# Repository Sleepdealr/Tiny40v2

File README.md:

# Tiny40v2

Please read the license.
Licensed under the Attribution-NonCommercial-ShareAlike 4.0 International

40% PCB with the equinox layout

Using the RP2040

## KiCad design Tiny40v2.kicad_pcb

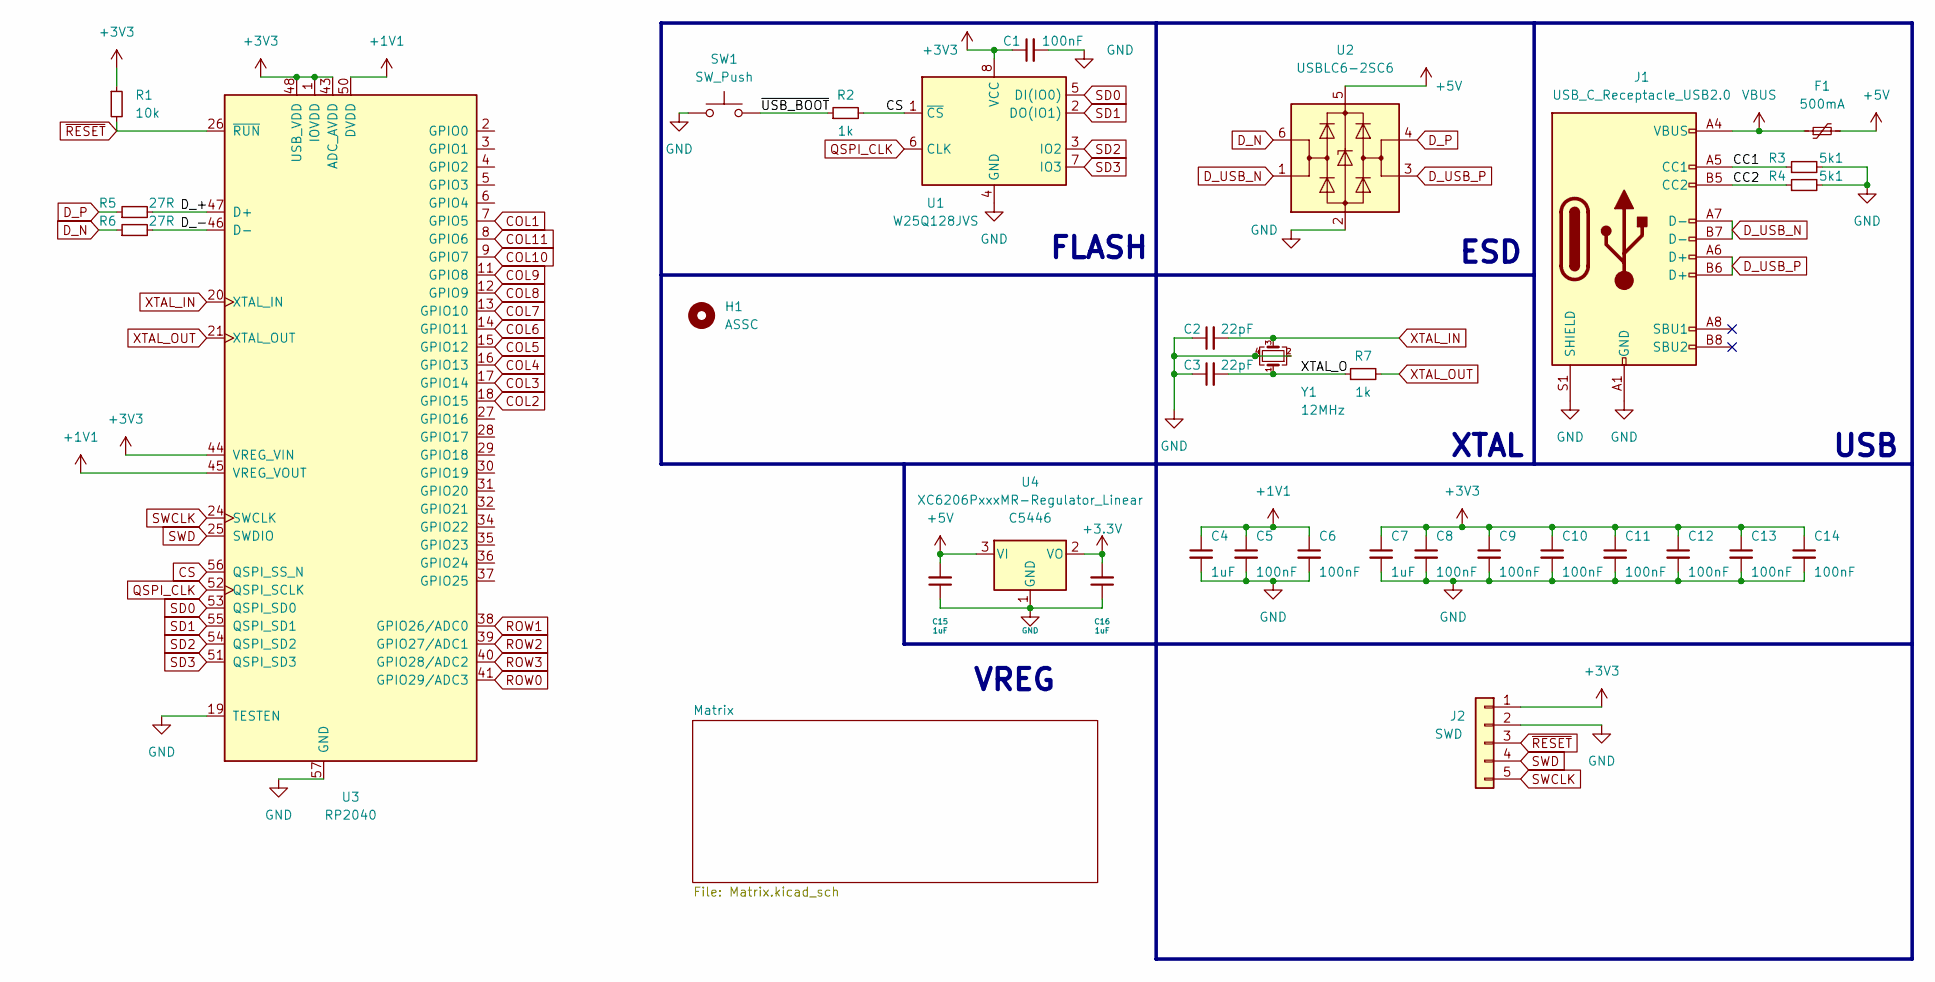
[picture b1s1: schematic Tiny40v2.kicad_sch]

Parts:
C1, C5, C6, C8, C9, C10, C11, C12, C13, C14: 100nF; C_0402_1005Metric; LCSC C1525
C2, C3: 22pF; C_0402_1005Metric; LCSC C1555
C4, C7, C15, C16: 1uF; C_0402_1005Metric; LCSC C52923
F1: 500mA; Fuse_1206_3216Metric; LCSC C70076
H1: ASSC; assc_fixed
J1: USB_C_Receptacle_USB2.0; USB_C_Receptacle_HRO_TYPE-C-31-M-12; LCSC C165948
J2: SWD; PinSocket_1x05_P2.54mm_Vertical
R1: 10k; R_0402_1005Metric; LCSC C25744
R2, R7: 1k; R_0402_1005Metric; LCSC C11702
R3, R4: 5k1; R_0402_1005Metric; LCSC C25905
R5, R6: 27R; R_0603_1608Metric; LCSC C25190
SW1: SW_Push; PinSocket_1x02_P2.54mm_Vertical
U1: W25Q128JVS; SOIC-8_5.23x5.23mm_P1.27mm; LCSC C131025
U2: USBLC6-2SC6; SOT-23-6; LCSC C2827654
U3: RP2040; RP2040-QFN-56; LCSC C2040
U4: XC6206PxxxMR-Regulator_Linear; SOT-23; LCSC C5446
Y1: 12MHz; Crystal_SMD_3225-4Pin_3.2x2.5mm; LCSC C97242

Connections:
+1V1: C4.1, C5.1, C6.1, U3.23 (DVDD), U3.45 (VREG_VOUT), U3.50 (DVDD)
+5V: C15.2, F1.2, U2.5 (VBUS), U4.3 (VI)
/CC1: J1.A5 (CC1), R3.1
/CC2: J1.B5 (CC2), R4.1
/D_+: R5.2, U3.47 (D+)
/D_-: R6.2, U3.46 (D-)
/XTAL_O: C3.2, R7.1, Y1.1
/~USB_BOOT: R2.1, SW1.2
COL1: U3.7 (GPIO5); also elsewhere on the board
COL2: U3.18 (GPIO15); also elsewhere on the board
COL3: U3.17 (GPIO14); also elsewhere on the board
COL4: U3.16 (GPIO13); also elsewhere on the board
COL5: U3.15 (GPIO12); also elsewhere on the board
COL6: U3.14 (GPIO11); also elsewhere on the board
COL7: U3.13 (GPIO10); also elsewhere on the board
COL8: U3.12 (GPIO9); also elsewhere on the board
COL9: U3.11 (GPIO8); also elsewhere on the board
COL10: U3.9 (GPIO7); also elsewhere on the board
COL11: U3.8 (GPIO6); also elsewhere on the board
CS: R2.2, U1.1 (~CS), U3.56 (QSPI_SS_N)
D_N: R6.1, U2.6 (I/O1)
D_P: R5.1, U2.4 (I/O2)
D_USB_N: J1.A7 (D-), J1.B7 (D-), U2.1 (I/O1)
D_USB_P: J1.A6 (D+), J1.B6 (D+), U2.3 (I/O2)
GND: C1.2, C2.1, C3.1, C4.2, C5.2, C6.2, C7.2, C8.2, C9.2, C10.2, C11.2, C12.2, C13.2, C14.2, C15.1, C16.1, J1.A1 (GND), J1.A12 (GND), J1.B1 (GND), J1.B12 (GND), J1.S1 (SHIELD), J2.2, R3.2, R4.2, SW1.1, U1.4 (GND), U2.2 (GND), U3.19 (TESTEN), U3.57 (GND), U4.1 (GND), Y1.2, Y1.4
QSPI_CLK: U1.6 (CLK), U3.52 (QSPI_SCLK)
ROW0: U3.41 (GPIO29/ADC3); also elsewhere on the board
ROW1: U3.38 (GPIO26/ADC0); also elsewhere on the board
ROW2: U3.39 (GPIO27/ADC1); also elsewhere on the board
ROW3: U3.40 (GPIO28/ADC2); also elsewhere on the board
SD0: U1.5 (DI(IO0)), U3.53 (QSPI_SD0)
SD1: U1.2 (DO(IO1)), U3.55 (QSPI_SD1)
SD2: U1.3 (IO2), U3.54 (QSPI_SD2)
SD3: U1.7 (IO3), U3.51 (QSPI_SD3)
SWCLK: J2.5, U3.24 (SWCLK)
SWD: J2.4, U3.25 (SWDIO)
VBUS: F1.1, J1.A4 (VBUS), J1.A9 (VBUS), J1.B4 (VBUS), J1.B9 (VBUS)
XTAL_IN: C2.2, U3.20 (XTAL_IN), Y1.3
XTAL_OUT: R7.2, U3.21 (XTAL_OUT)
~RESET: J2.3, R1.2, U3.26 (~RUN)

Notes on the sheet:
USB
VREG
ESD
XTAL
FLASH

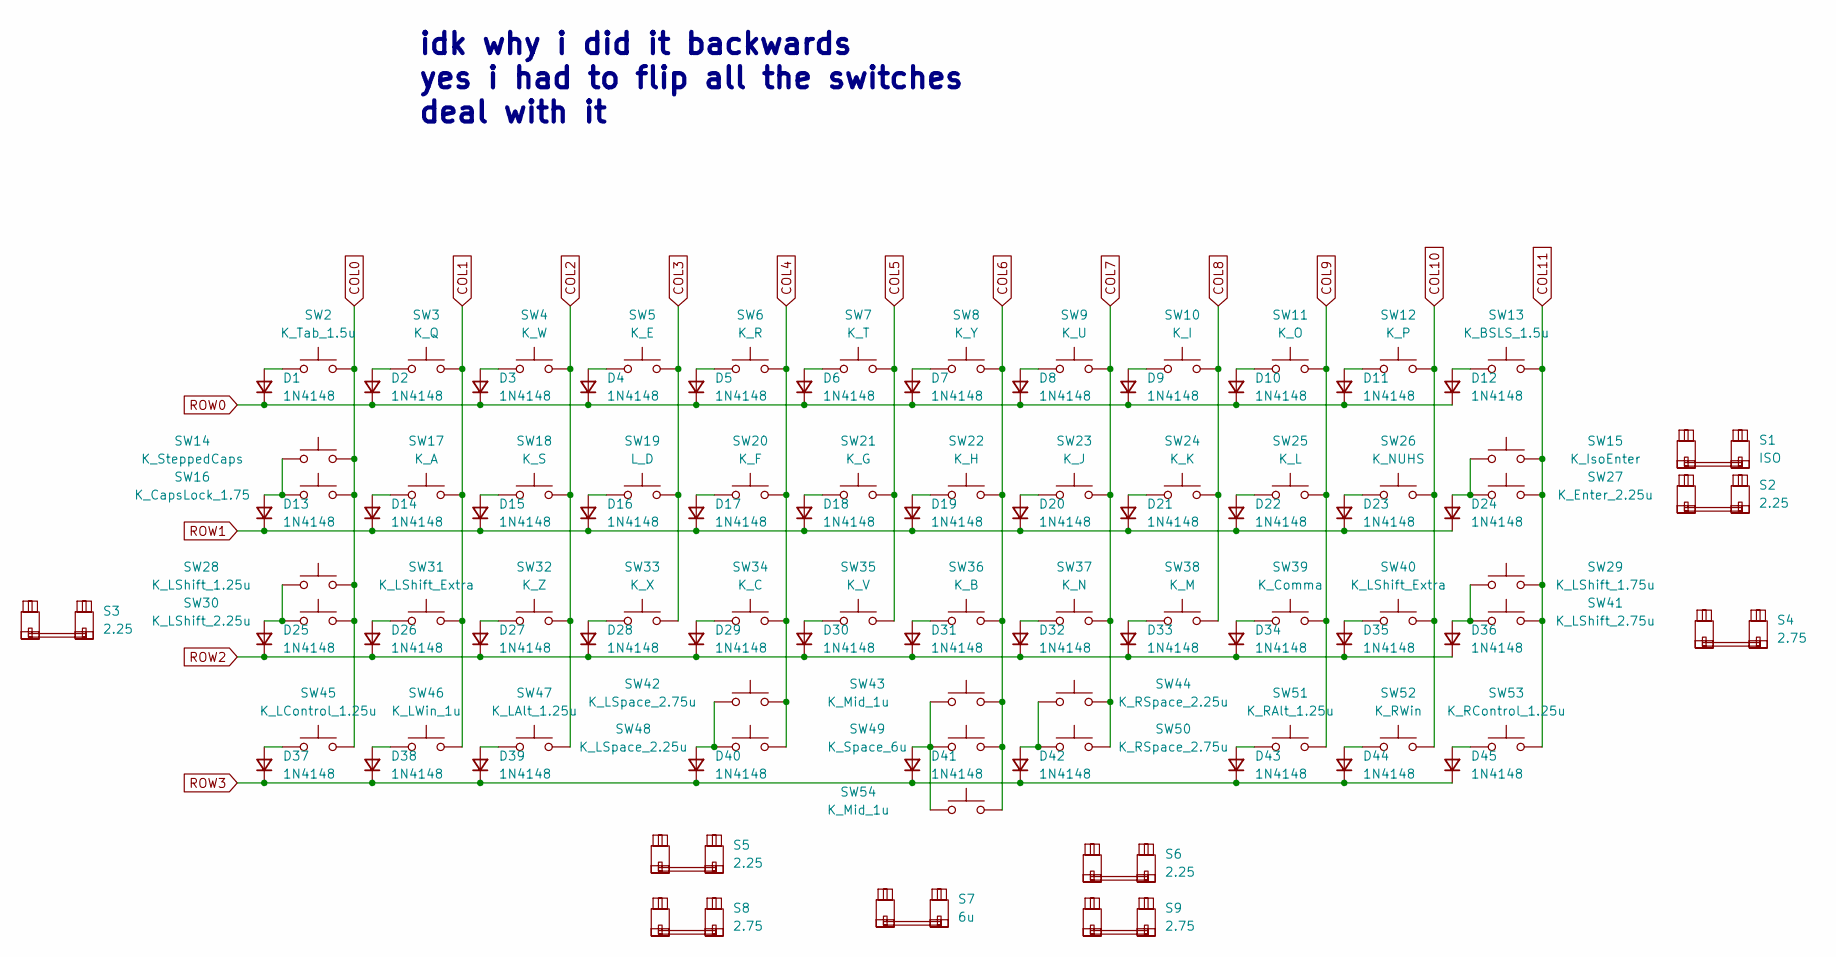
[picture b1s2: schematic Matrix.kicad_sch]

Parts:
D1, D2, D3, D4, D5, D6, D7, D8, D9, D10, D11, D12, D13, D14, D15, D16, D17, D18, D19, D20, D21, D22, D23, D24, D25, D26, D27, D28, D29, D30, D31, D32, D33, D34, D35, D36, D37, D38, D39, D40, D41, D42, D43, D44, D45: 1N4148; D_SOD-123
S1: ISO; STAB_MX_ISO_FLIPPED
S2, S3, S5, S6: 2.25; STAB_MX_2.25u
S4, S8, S9: 2.75; STAB_MX_2.75u
S7: 6u; STAB_MX_6u
SW2: K_Tab_1.5u; SW_MX_1.5u
SW3: K_Q; SW_MX_1u
SW4: K_W; SW_MX_1u
SW5: K_E; SW_MX_1u
SW6: K_R; SW_MX_1u
SW7: K_T; SW_MX_1u
SW8: K_Y; SW_MX_1u
SW9: K_U; SW_MX_1u
SW10: K_I; SW_MX_1u
SW11: K_O; SW_MX_1u
SW12: K_P; SW_MX_1u
SW13: K_BSLS_1.5u; SW_MX_1.5u
SW14: K_SteppedCaps; SW_MX_1.75u_stp
SW15: K_IsoEnter; SW_MX_1u
SW16: K_CapsLock_1.75; SW_MX_1.75u
SW17: K_A; SW_MX_1u
SW18: K_S; SW_MX_1u
SW19: L_D; SW_MX_1u
SW20: K_F; SW_MX_1u
SW21: K_G; SW_MX_1u
SW22: K_H; SW_MX_1u
SW23: K_J; SW_MX_1u
SW24: K_K; SW_MX_1u
SW25: K_L; SW_MX_1u
SW26: K_NUHS; SW_MX_1u
SW27: K_Enter_2.25u; SW_MX_1u
SW28: K_LShift_1.25u; SW_MX_1.25u
SW29: K_LShift_1.75u; SW_MX_1.75u
SW30: K_LShift_2.25u; SW_MX_1u
SW31, SW40: K_LShift_Extra; SW_MX_1u
SW32: K_Z; SW_MX_1u
SW33: K_X; SW_MX_1u
SW34: K_C; SW_MX_1u
SW35: K_V; SW_MX_1u
SW36: K_B; SW_MX_1u
SW37: K_N; SW_MX_1u
SW38: K_M; SW_MX_1u
SW39: K_Comma; SW_MX_1u
SW41: K_LShift_2.75u; SW_MX_1u
SW42: K_LSpace_2.75u; SW_MX_1u
SW43, SW54: K_Mid_1u; SW_MX_1u
SW44: K_RSpace_2.25u; SW_MX_1u
SW45: K_LControl_1.25u; SW_MX_1.25u
SW46: K_LWin_1u; SW_MX_1u
SW47: K_LAlt_1.25u; SW_MX_1.25u
SW48: K_LSpace_2.25u; SW_MX_1u
SW49: K_Space_6u; SW_MX_1u
SW50: K_RSpace_2.75u; SW_MX_1u
SW51: K_RAlt_1.25u; SW_MX_1.25u
SW52: K_RWin; SW_MX_1u
SW53: K_RControl_1.25u; SW_MX_1.25u

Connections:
COL0: SW2.1, SW14.1, SW16.1, SW28.1, SW30.1, SW45.1
COL1: SW3.1, SW17.1, SW31.1, SW46.1; also elsewhere on the board
COL2: SW4.1, SW18.1, SW32.1, SW47.1; also elsewhere on the board
COL3: SW5.1, SW19.1, SW33.1; also elsewhere on the board
COL4: SW6.1, SW20.1, SW34.1, SW42.1, SW48.1; also elsewhere on the board
COL5: SW7.1, SW21.1, SW35.1; also elsewhere on the board
COL6: SW8.1, SW22.1, SW36.1, SW43.1, SW49.1, SW54.1; also elsewhere on the board
COL7: SW9.1, SW23.1, SW37.1, SW44.1, SW50.1; also elsewhere on the board
COL8: SW10.1, SW24.1, SW38.1; also elsewhere on the board
COL9: SW11.1, SW25.1, SW39.1, SW51.1; also elsewhere on the board
COL10: SW12.1, SW26.1, SW40.1, SW52.1; also elsewhere on the board
COL11: SW13.1, SW15.1, SW27.1, SW29.1, SW41.1, SW53.1; also elsewhere on the board
unnamed: D1.2 (A), SW2.2
unnamed: D2.2 (A), SW3.2
unnamed: D3.2 (A), SW4.2
unnamed: D4.2 (A), SW5.2
unnamed: D5.2 (A), SW6.2
unnamed: D6.2 (A), SW7.2
unnamed: D7.2 (A), SW8.2
unnamed: D8.2 (A), SW9.2
unnamed: D9.2 (A), SW10.2
unnamed: D10.2 (A), SW11.2
unnamed: D11.2 (A), SW12.2
unnamed: D12.2 (A), SW13.2
unnamed: D13.2 (A), SW14.2, SW16.2
unnamed: D14.2 (A), SW17.2
unnamed: D15.2 (A), SW18.2
unnamed: D16.2 (A), SW19.2
unnamed: D17.2 (A), SW20.2
unnamed: D18.2 (A), SW21.2
unnamed: D19.2 (A), SW22.2
unnamed: D20.2 (A), SW23.2
unnamed: D21.2 (A), SW24.2
unnamed: D22.2 (A), SW25.2
unnamed: D23.2 (A), SW26.2
unnamed: D24.2 (A), SW15.2, SW27.2
unnamed: D25.2 (A), SW28.2, SW30.2
unnamed: D26.2 (A), SW31.2
unnamed: D27.2 (A), SW32.2
unnamed: D28.2 (A), SW33.2
unnamed: D29.2 (A), SW34.2
unnamed: D30.2 (A), SW35.2
unnamed: D31.2 (A), SW36.2
unnamed: D32.2 (A), SW37.2
unnamed: D33.2 (A), SW38.2
unnamed: D34.2 (A), SW39.2
unnamed: D35.2 (A), SW40.2
unnamed: D36.2 (A), SW29.2, SW41.2
unnamed: D37.2 (A), SW45.2
unnamed: D38.2 (A), SW46.2
unnamed: D39.2 (A), SW47.2
unnamed: D40.2 (A), SW42.2, SW48.2
unnamed: D41.2 (A), SW43.2, SW49.2, SW54.2
unnamed: D42.2 (A), SW44.2, SW50.2
unnamed: D43.2 (A), SW51.2
unnamed: D44.2 (A), SW52.2
unnamed: D45.2 (A), SW53.2
ROW0: D1.1 (K), D2.1 (K), D3.1 (K), D4.1 (K), D5.1 (K), D6.1 (K), D7.1 (K), D8.1 (K), D9.1 (K), D10.1 (K), D11.1 (K), D12.1 (K); also elsewhere on the board
ROW1: D13.1 (K), D14.1 (K), D15.1 (K), D16.1 (K), D17.1 (K), D18.1 (K), D19.1 (K), D20.1 (K), D21.1 (K), D22.1 (K), D23.1 (K), D24.1 (K); also elsewhere on the board
ROW2: D25.1 (K), D26.1 (K), D27.1 (K), D28.1 (K), D29.1 (K), D30.1 (K), D31.1 (K), D32.1 (K), D33.1 (K), D34.1 (K), D35.1 (K), D36.1 (K); also elsewhere on the board
ROW3: D37.1 (K), D38.1 (K), D39.1 (K), D40.1 (K), D41.1 (K), D42.1 (K), D43.1 (K), D44.1 (K), D45.1 (K); also elsewhere on the board

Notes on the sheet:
idk why i did it backwards yes i had to flip all the switches deal with it

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
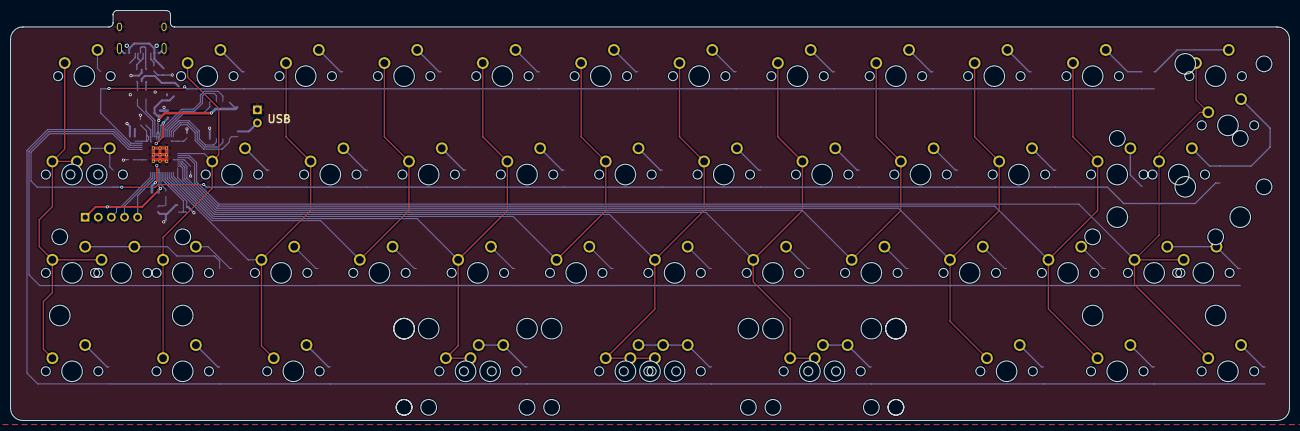
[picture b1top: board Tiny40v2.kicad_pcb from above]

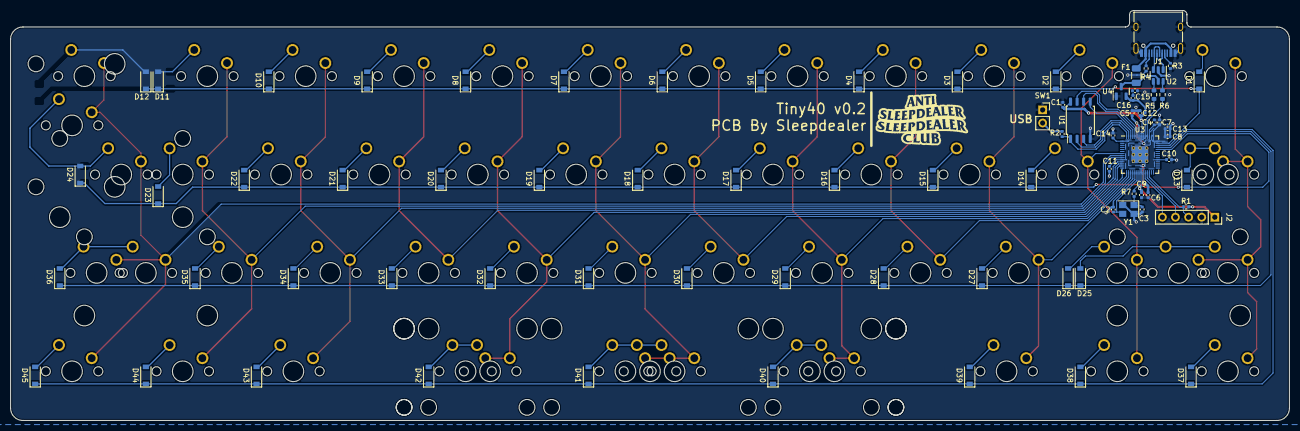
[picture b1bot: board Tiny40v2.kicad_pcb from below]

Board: 2 copper layers, 247.7 x 79.4 mm, 140 parts (78 on the bottom side), 87 nets.

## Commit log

2022-02-04 Init
2022-02-04 Add LICENSE
2022-02-09 Updat e LICENSE
